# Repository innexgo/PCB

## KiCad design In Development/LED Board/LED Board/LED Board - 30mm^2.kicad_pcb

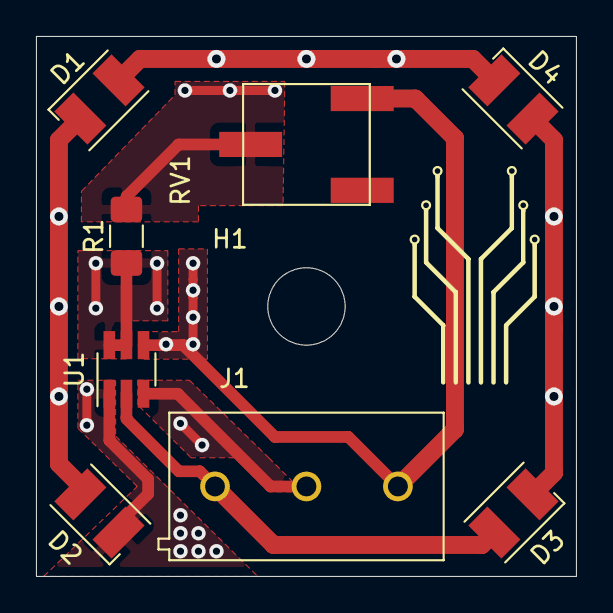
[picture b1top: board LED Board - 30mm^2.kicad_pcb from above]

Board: 2 copper layers, 30.0 x 30.0 mm, 9 parts (0 on the bottom side), 9 nets.

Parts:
D1, D2, D3, D4: LED_ALT; LED_PLCC-2
H1: MountingHole; MountingHole_4.3mm_M4
J1: Screw_Terminal_01x03; TE-C_3_Pos_Buchanan_Screw_Terminal
R1: 43; R_1206_3216Metric_Pad1.42x1.75mm_HandSolder
RV1: 20; Bourns_3361_Pot
U1: AL5802; SOT-23-6_Handsoldering

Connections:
/EN: J1.2, U1.3
GND: J1.3, RV1.3, U1.4
unnamed: D1.1, D2.2
unnamed: D1.2, D4.1
unnamed: D2.1, U1.1
unnamed: D3.1, D4.2
unnamed: R1.1, U1.5, U1.6
unnamed: R1.2, RV1.2
VCC: D3.2, J1.1, U1.2

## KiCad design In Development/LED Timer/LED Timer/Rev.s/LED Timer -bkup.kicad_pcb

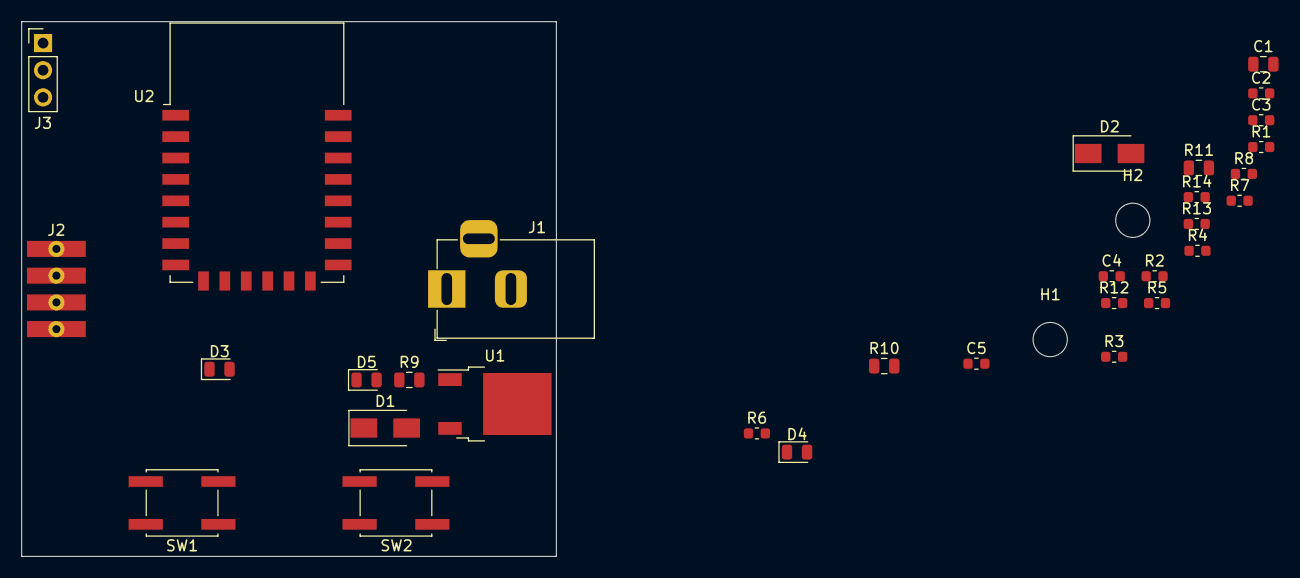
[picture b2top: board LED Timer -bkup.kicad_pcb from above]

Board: 2 copper layers, 50.0 x 50.0 mm, 33 parts (0 on the bottom side), 21 nets, no tracks yet.

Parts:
C1: 0.33uF; C_0805_2012Metric
C2, C3, C4: 0.1uF; C_0603_1608Metric
C5: 1uF DNP; C_0603_1608Metric
D1, D2: Diode; D_SMA
D3, D4: Blue 3.2; LED_0805_2012Metric
D5: Red 2; LED_0805_2012Metric
H1, H2: MountingHole; MountingHole_3.2mm_M3
J1: Barrel_Jack_Switch; BarrelJack_Horizontal
J2: Conn_01x04_Male; 4x_1.5mm_5.5mm_bare_copper_+THT
J3: Conn_01x03_Female; PinHeader_1x03_P2.54mm_Vertical
R1, R2, R3, R4, R5, R14: 12K; R_0603_1608Metric
R6, R8: 22; R_0603_1608Metric
R7, R13: 470; R_0603_1608Metric
R9: 510; R_0805_2012Metric
R10: 220K 1% DNP; R_0805_2012Metric
R11: 100k 1% DNP; R_0805_2012Metric
R12: 2.2K DNP; R_0603_1608Metric
SW1: DNP; SW_SPST_EVQQ2
SW2: SW2; SW_SPST_EVQQ2
U1: LM7805_TO252-2; TO-252-2
U2: ESP-12E

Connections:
+3.3VA: C4.1, D1.1, J3.1, R1.1, R2.1, R3.1, R4.1, R6.1, R8.1, R12.2, R14.1, U2.8
+5V: C2.1, D1.2, U1.3
+12V: C1.2, J1.1, J2.4, R9.2, U1.1
/0VA: C3.2, C4.2, D2.2, D4.1, J3.3, R5.1, R11.1, SW1.2, SW2.2, U2.15
/ADC: R10.1, R11.2, U2.2
/EN: R4.2, U2.3
/EXT_ADC: C5.1, R10.2
/GPIO0: R1.2, U2.18
/GPIO2: R2.2, U2.17
/GPIO5: R13.1, R14.2, U2.20
/GPIO13: J2.2, J2.3, U2.7
/GPIO15: R5.2, U2.16
/GPIO16: D3.1, U2.4
/RST: C3.1, R3.2, R7.1, U2.1
GND: C1.1, C2.2, D2.1, D5.1, J1.2, J1.3, J2.1, U1.2
unnamed: C5.2, J3.2, R12.1
unnamed: D3.2, R6.2
unnamed: D4.2, R8.2
unnamed: D5.2, R9.1
unnamed: R7.2, SW1.1
unnamed: R13.2, SW2.1

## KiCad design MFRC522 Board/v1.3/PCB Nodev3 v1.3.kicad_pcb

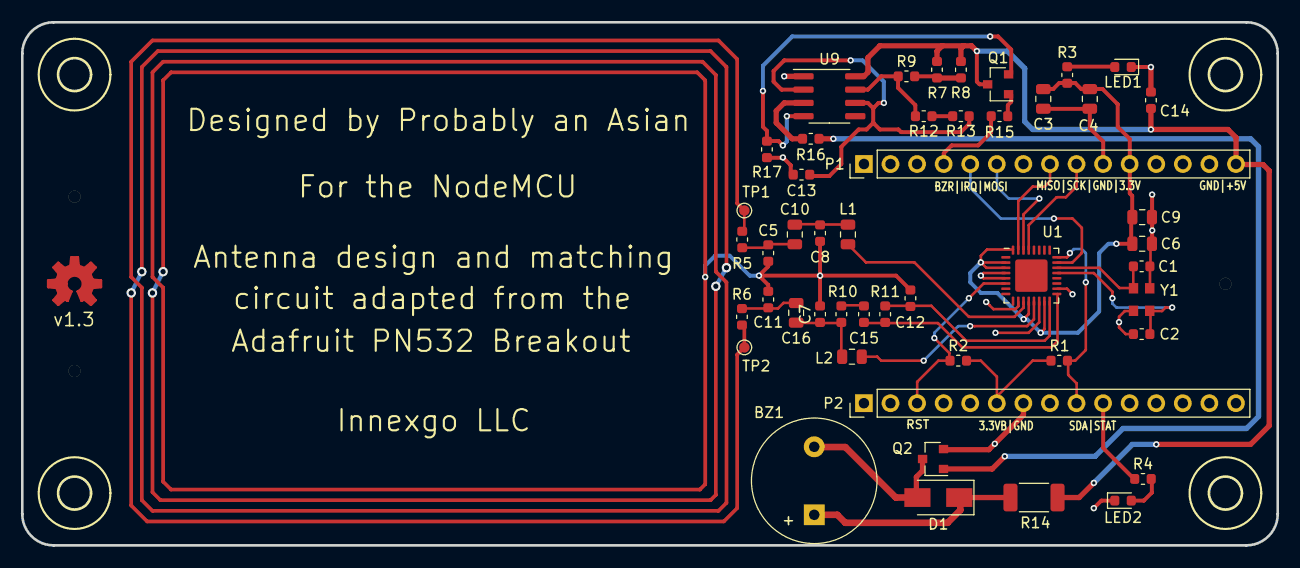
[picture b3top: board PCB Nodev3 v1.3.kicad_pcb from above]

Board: 2 copper layers, 120.0 x 50.0 mm, 56 parts (0 on the bottom side), 35 nets.

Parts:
1: OSHW-LOGOM; OSHWLOGO_TOP_0.2
BZ1: Buzzer; Buzzer_12x9.5RM6.5
C1, C2: 33pF; C_0603_1608Metric
C3, C4: C_Small; C_0805_2012Metric
C5, C11: 100pF; C_0603_1608Metric
C6, C9: 1uF; C_0805_2012Metric
C7, C8: 220pF; C_0603_1608Metric
C10, C16: 22pF; C_0805_2012Metric
C12: 100nF; C_0603_1608Metric
C13: 22nF; C_0603_1608Metric
C14: 10nF; C_0603_1608Metric
C15: 1nF; C_0603_1608Metric
D1: D_Schottky; D_SMA
L1, L2: 560nH; L_0805_2012Metric
LED1, LED2: LED; LED_0603_1608Metric
P1: ESP32 NODEMCU DEVKIT1 LEFT HEADER-MALE-2.54; PinHeader_1x15_P2.54mm_Vertical
P2: ESP32 NODEMCU DEVKIT1 RIGHT HEADER-MALE-2.54; PinHeader_1x15_P2.54mm_Vertical
Q1, Q2: Q_NPN_BEC; SOT-23
R1, R2, R11: 1.0K; R_0603_1608Metric
R3: 15; R_0603_1608Metric
R4: 24; R_0603_1608Metric
R5, R6: 1.5; R_0603_1608Metric
R7, R8: 18K; R_0603_1608Metric
R9: 68; R_0603_1608Metric
R10: 1.69K; R_0603_1608Metric
R12: 68K; R_0603_1608Metric
R13: 2K; R_0603_1608Metric
R14: 39; R_2010_5025Metric
R15: 9.1K; R_0603_1608Metric
R16: 200; R_0603_1608Metric
R17: 3.3K; R_0603_1608Metric
TP1, TP2: TestPoint_Probe; TestPoint_Pad_D1.0mm
U1: MFRC522; QFN-32-1EP_5x5mm_P0.5mm_EP3.1x3.1mm
U2, U3, U4, U5: 3,0; MOUNTINGHOLE_3.0
U6, U7, U8: Tooling Hole; TOOLING_HOLE_JLCPCB
U9: NE555; SOIC-8_3.9x4.9mm_P1.27mm
Y1: 27.12 MHz; Oscillator_SMD_EuroQuartz_XO32-4Pin_3.2x2.5mm

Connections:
+3.3VA: P2.6, R1.2, R2.2
+3V3: C3.1, C4.1, C6.1, C9.1, P1.11, R3.1, U1.2, U1.3, U1.12, U1.15, U1.32
+5V: C14.1, P1.15, Q1.3, R7.2, R8.2, R14.1, U9.8
/BZROSC: R16.1, U9.3
/GPIO-TH: P1.4, R15.2
/IRQ: P1.5, U1.23
/MISO: P1.8, U1.31
/MOSI: P1.6, U1.30
/RST: P2.3, R2.1, U1.6
/SCK: P1.9, U1.29
/SDA: P2.9, R1.1, U1.24
/STATUS: P2.10, R4.1
GND: C1.1, C2.1, C3.2, C4.2, C5.1, C6.2, C7.2, C8.1, C9.2, C11.2, C12.1, C13.1, C14.2, LED1.1, LED2.1, P1.10, P1.14, P2.7, P2.14, Q2.2, R5.1, R6.2, R17.2, TP1.1, TP2.1, U1.4, U1.5, U1.10, U1.14, U1.18, U9.1, Y1.2, Y1.4
unnamed: BZ1.1, D1.1, R14.2
unnamed: BZ1.2, D1.2, Q2.3
unnamed: C1.2, U1.22, Y1.3
unnamed: C2.2, U1.21, Y1.1
unnamed: C8.2, C10.1, L1.1
unnamed: C5.2, C10.2, R5.2
unnamed: C11.1, C16.1, R6.1
unnamed: C12.2, R11.2, U1.16
unnamed: C13.2, R13.1, U9.2, U9.6
unnamed: C15.1, R11.1, U1.17
unnamed: C15.2, R10.1
unnamed: C7.1, C16.2, L2.2, R10.2
unnamed: L1.2, U1.11
unnamed: L2.1, U1.13
unnamed: LED1.2, R3.2
unnamed: LED2.2, R4.2
unnamed: Q1.1, R15.1
unnamed: Q1.2, R17.1, U9.4
unnamed: Q2.1, R16.2
unnamed: R7.1, R8.1, R9.2
unnamed: R12.1, R13.2
unnamed: R9.1, R12.2, U9.7
